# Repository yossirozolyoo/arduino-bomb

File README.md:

# Gravity/Methoda - Bomb exercise
This is the implementation of the bomb exercise made by Yossi Rosilio for Gravity and Methoda.

## Exercise goals
The exercise goals are:
- Practice the protocols UART, I2C and SPI
- Practice using a logic analyzer for decoding a protocol

Its secondary goals are:
- "Sell" digital protocols to the students in a fun way
- Improve team dynamics for the students

## Exercise dependencies
The exercise runs in the protocols unit, after the lecture.

## Running the exercise
1. After consulting with the staff, divide the class into groups of 1-3. The group size is based on how you think would be the best to run the exercise, considering the students' level, team dynamics, and available setups.
2. Build one setup for each group. Detailed explanation is in a separate section.
3. Connect the setup (Arduino UNO + Logic Analyzer) to the working station of the group. Make sure the hostname of that PC is documented for you.
4. From the teachers' PC, use `psexec` to run the bomb client web interface. Detailed explanation on how to run the web interface is in a separate section.
5. From the web interface, set the correct left time on the bomb (derived from the time allocated for the exercise), and the current level and level queue.

At that point the exercise should be running, waiting for the students to solve it. At the end of this document you can find tips for how to solve problems that can occure while running the exercise.

## Building the setup
TBD

## Controlling the bomb using the web interface
TBD

## Tips for running the exercise smoothly
* Prepare extra parts for repairing wires that were cut incorrectly.
* TBD

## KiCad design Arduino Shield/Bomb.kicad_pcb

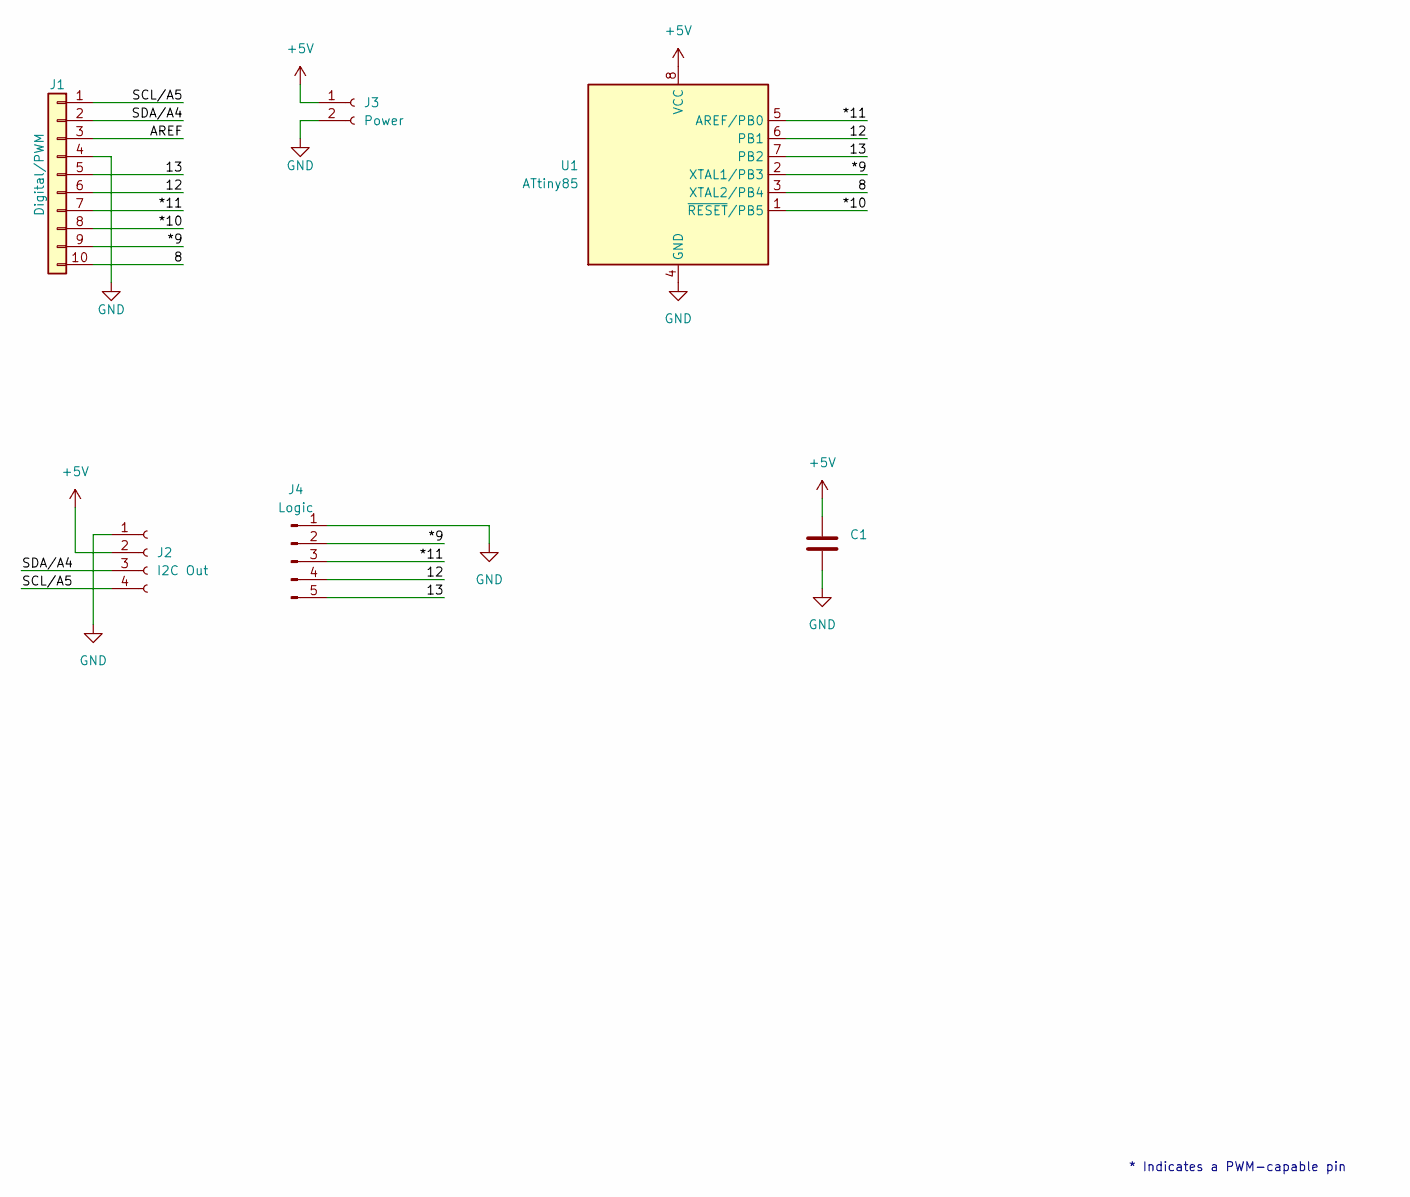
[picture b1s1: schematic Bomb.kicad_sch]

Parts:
C1: C; C_0504_1310Metric_Pad0.83x1.28mm_HandSolder
J1: Digital/PWM; PinSocket_1x10_P2.54mm_Vertical
J2: I2C Out; PinHeader_1x04_P2.54mm_Vertical
J3: Power; PinHeader_1x02_P2.54mm_Vertical
J4: Logic; PinHeader_1x05_P2.54mm_Vertical
U1: ATtiny85; DIP-8_W7.62mm

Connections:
+5V: C1.1, J2.2, J3.1, U1.8 (VCC)
/8: J1.10, U1.3 (XTAL2/PB4)
/12: J1.6, J4.4, U1.6 (PB1)
/13: J1.5, J4.5, U1.7 (PB2)
/*9: J1.9, J4.2, U1.2 (XTAL1/PB3)
/*10: J1.8, U1.1 (~RESET/PB5)
/*11: J1.7, J4.3, U1.5 (AREF/PB0)
/AREF: J1.3
/SCL/A5: J1.1, J2.4
/SDA/A4: J1.2, J2.3
GND: C1.2, J1.4, J2.1, J3.2, J4.1, U1.4 (GND)

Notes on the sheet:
* Indicates a PWM-capable pin

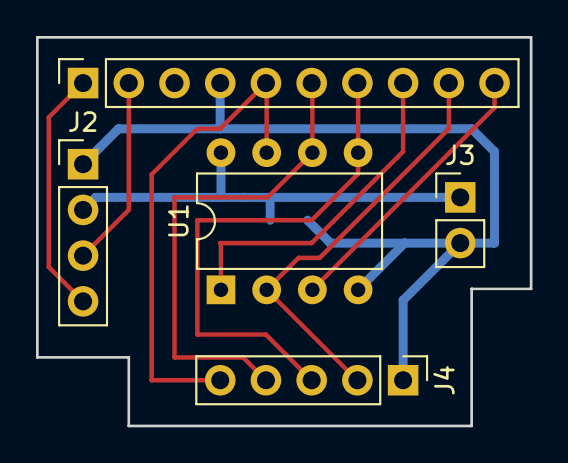
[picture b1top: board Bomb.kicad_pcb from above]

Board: 2 copper layers, 27.4 x 21.6 mm, 6 parts (1 on the bottom side), 10 nets.

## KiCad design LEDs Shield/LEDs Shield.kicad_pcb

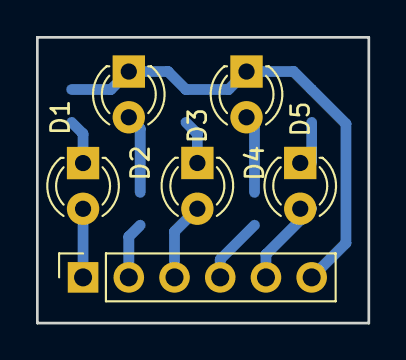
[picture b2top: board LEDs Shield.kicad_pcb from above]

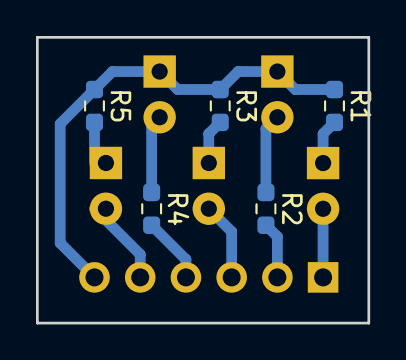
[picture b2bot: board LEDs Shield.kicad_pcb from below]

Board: 2 copper layers, 18.4 x 15.9 mm, 11 parts (5 on the bottom side), 11 nets.

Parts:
D1, D2, D3, D4, D5: LED; LED_D3.0mm
J3: LEDs and GND; PinSocket_1x06_P2.54mm_Vertical
R1, R2, R3, R4, R5: 300; R_0603_1608Metric_Pad0.98x0.95mm_HandSolder

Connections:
GND: D2.1 (K), D4.1 (K), J3.6, R1.1, R3.1, R5.1
unnamed: D1.1 (K), R1.2
unnamed: D2.2 (A), R2.1
unnamed: D3.1 (K), R3.2
unnamed: D4.2 (A), R4.1
unnamed: D5.1 (K), R5.2
unnamed: D1.2 (A), J3.1
unnamed: J3.2, R2.2
unnamed: D3.2 (A), J3.3
unnamed: J3.4, R4.2
unnamed: D5.2 (A), J3.5

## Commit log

2023-01-23 Working version of the bomb
2023-01-29 Added shield board design files
2023-01-29 Added markings near the GND and 5V, added capacitor between 5V and GND, generated fabrication files
2023-01-29 Added LED shield hardware files
2023-01-29 Updated UNO shield's gerber files
2023-01-30 Added support for management server, implemented an ipython client
2023-02-01 Added support for leds, changed bomb wiring
2023-02-01 Widened the pads of C1 in the arduino shield, switched the pinout of the i2c out, adjusted the size of the arduino shield board
2023-02-03 Added LED animation in level transitions
2023-02-03 Added support for setting the left time, and support for recieving commands while on done and fail
2023-02-03 Added support for getting/setting the bomb level from the bomb client
2023-02-05 Added support for level queues
2023-02-05 Reduced clock stretching in spi caused by refresh_screen (unchecked SPI logic)
2023-02-05 Synchronized ATtiny85 after finishing I2C level
2023-02-05 Cleared read buffer before sending a command
2023-02-12 Added a flask application to BombClient which controls the bomb
2023-02-12 Removed unnecessary files
2023-02-12 Added gitignore
2023-02-13 Added the basic structure of README.md
